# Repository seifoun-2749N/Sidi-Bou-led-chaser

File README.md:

# Sidi-Bou-led-chaser

---

# Overview :
A custom led chaser project made by following the Blinky Starter Project tutorial from Blueprint HackClub. It's PCB shape refers to the traditional door of Sidi Bou Said situated in Tunisa.

---

# Hardware :
- NE555P Timer
- 4017 IC
- 2 Resistors(1k ohm and 470 ohm)
- 1 Potentiometer
- 1 Normal Capacitor
- 1 Polarized Capacitor
- 10 LEDs

---

# 3D Overview :

## Front View 

## Rear View

## Schematics

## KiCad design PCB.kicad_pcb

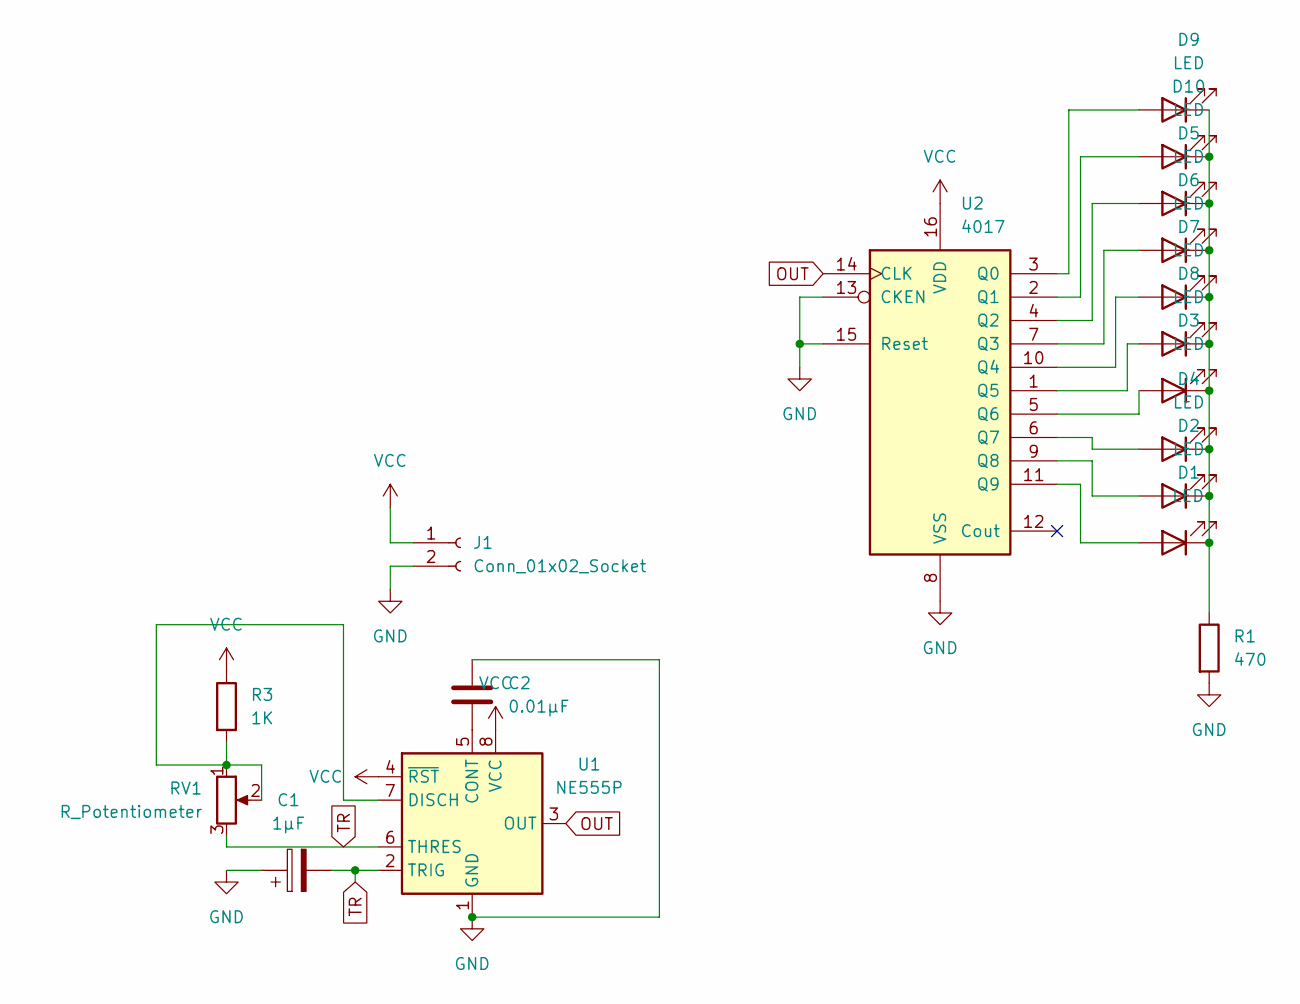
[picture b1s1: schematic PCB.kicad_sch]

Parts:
C1: 1µF; CP_Radial_D5.0mm_P2.00mm
C2: 0.01µF; C_Disc_D7.0mm_W2.5mm_P5.00mm
D1, D2, D3, D4, D5, D6, D7, D8, D9, D10: LED; LED_D3.0mm
J1: Conn_01x02_Socket; PinHeader_1x02_P2.54mm_Vertical
R1: 470; R_Axial_DIN0207_L6.3mm_D2.5mm_P7.62mm_Horizontal
R3: 1K; R_Axial_DIN0207_L6.3mm_D2.5mm_P7.62mm_Horizontal
RV1: R_Potentiometer; Potentiometer_Vishay_T93YA_Vertical
U1: NE555P; DIP-8_W7.62mm
U2: 4017; N16

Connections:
GND: C1.1, C2.1, J1.2, R1.2, U1.1 (GND), U2.8 (VSS), U2.13 (CKEN), U2.15 (Reset)
unnamed: D1.2 (A), U2.11 (Q9)
unnamed: D1.1 (K), D2.1 (K), D3.1 (K), D4.1 (K), D5.1 (K), D6.1 (K), D7.1 (K), D8.1 (K), D9.1 (K), D10.1 (K), R1.1
unnamed: D2.2 (A), U2.9 (Q8)
unnamed: D3.2 (A), U2.5 (Q6)
unnamed: D4.2 (A), U2.6 (Q7)
unnamed: D5.2 (A), U2.4 (Q2)
unnamed: D6.2 (A), U2.7 (Q3)
unnamed: D7.2 (A), U2.10 (Q4)
unnamed: D8.2 (A), U2.1 (Q5)
unnamed: D9.2 (A), U2.3 (Q0)
unnamed: D10.2 (A), U2.2 (Q1)
unnamed: C2.2, U1.5 (CONT)
unnamed: R3.2, RV1.1, RV1.2, U1.7 (DISCH)
OUT: U1.3 (OUT), U2.14 (CLK)
TR: C1.2, RV1.3, U1.2 (TRIG), U1.6 (THRES)
VCC: J1.1, R3.1, U1.4 (~RST), U1.8 (VCC), U2.16 (VDD)

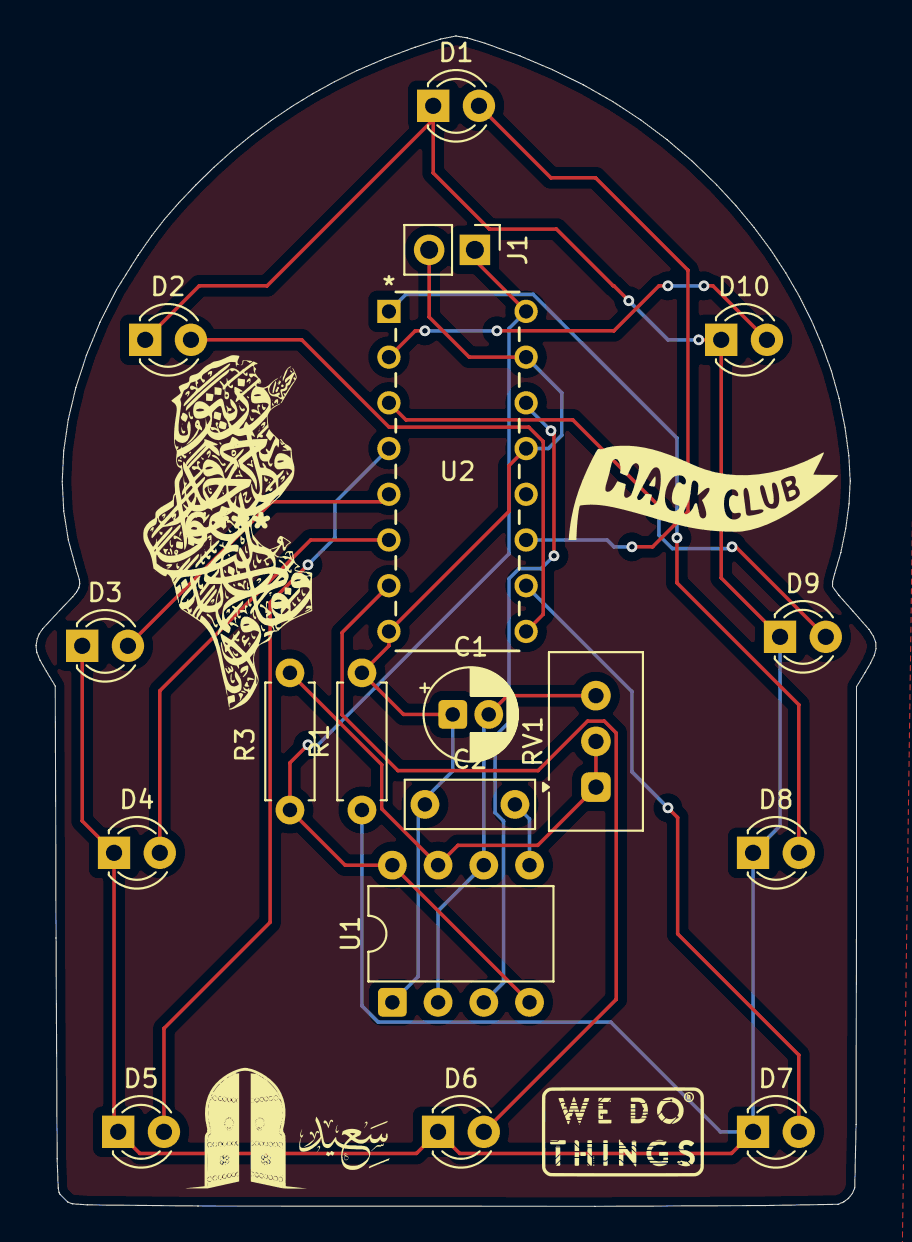
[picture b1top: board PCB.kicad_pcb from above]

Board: 2 copper layers, 46.7 x 65.0 mm, 18 parts (0 on the bottom side), 17 nets.
